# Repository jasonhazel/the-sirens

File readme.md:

# The Sirens

38/44/48/56 key split

## WORK IN PROGRESS

<p xmlns:cc="http://creativecommons.org/ns#" xmlns:dct="http://purl.org/dc/terms/"><a property="dct:title" rel="cc:attributionURL" href="https://github.com/jasonhazel/the-sirens">The Sirens</a> by <a rel="cc:attributionURL dct:creator" property="cc:attributionName" href="https://github.com/jasonhazel">Jason Hazel</a> is licensed under <a href="http://creativecommons.org/licenses/by/4.0/?ref=chooser-v1" target="_blank" rel="license noopener noreferrer" style="display:inline-block;">CC BY 4.0</a></p>

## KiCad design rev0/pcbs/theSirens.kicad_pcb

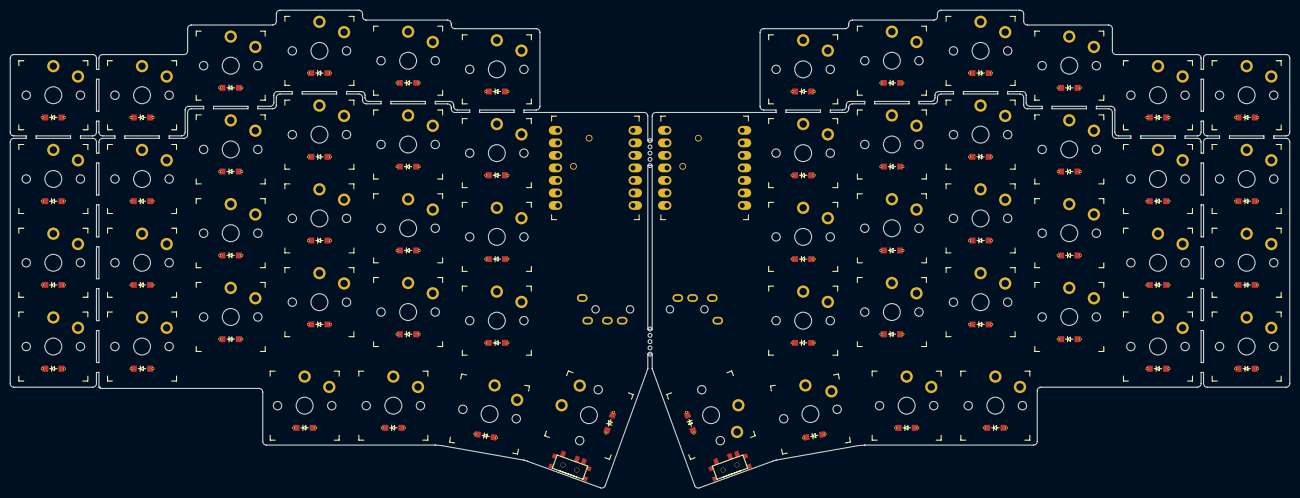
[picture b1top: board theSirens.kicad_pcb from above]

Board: 2 copper layers, 259.7 x 97.0 mm, 118 parts (0 on the bottom side), 78 nets, no tracks yet.

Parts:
74HC595, 74HC595#2: 74HC595_SOIC-16_3.9x9.9mm_P1.27mm
D1, D2, D3, D4, D5, D6, D7, D8, D9, D10, D11, D12, D13, D14, D15, D16, D17, D18, D19, D20, D21, D22, D23, D24, D25, D26, D27, D28, D29, D30, D31, D32, D33, D34, D35, D36, D37, D38, D39, D40, D41, D42, D43, D44, D45, D46, D47, D48, D49, D50, D51, D52, D53, D54, D55, D56: ComboDiode
S1, S2, S3, S4, S5, S6, S7, S8, S9, S10, S11, S12, S13, S14, S15, S16, S17, S18, S19, S20, S21, S22, S23, S24, S25, S26, S27, S28, S29, S30, S31, S32, S33, S34, S35, S36, S37, S38, S39, S40, S41, S42, S43, S44, S45, S46, S47, S48, S49, S50, S51, S52, S53, S54, S55, S56: PG1350
T1, T2: SPDT_C128955
XIAO1, XIAO2: xiao-ble-tht

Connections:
3V3: 74HC595.10, 74HC595.16, 74HC595#2.10, 74HC595#2.16, XIAO1.12, XIAO2.12
BAT: XIAO1.19, XIAO2.19
BAT-: T1.1, T2.1
GND: 74HC595.8, 74HC595.13, 74HC595#2.8, 74HC595#2.13, T1.2, T2.2, XIAO1.13, XIAO2.13
MISO: XIAO1.10, XIAO2.10
MOSI: 74HC595.14, 74HC595#2.14, XIAO1.11, XIAO2.11
RAW: XIAO1.14, XIAO2.14
RST: XIAO1.17, XIAO2.17
SCK: 74HC595.11, 74HC595#2.11, XIAO1.9, XIAO2.9
SR_CS: 74HC595.12, 74HC595#2.12
c0: 74HC595.1, 74HC595#2.1, S21.2, S22.2, S23.2, S24.2, S49.2, S50.2, S51.2, S52.2
c1: 74HC595.2, 74HC595#2.2, S17.2, S18.2, S19.2, S20.2, S45.2, S46.2, S47.2, S48.2
c2: 74HC595.3, 74HC595#2.3, S13.2, S14.2, S15.2, S16.2, S41.2, S42.2, S43.2, S44.2
c3: 74HC595.4, 74HC595#2.4, S9.2, S10.2, S11.2, S12.2, S37.2, S38.2, S39.2, S40.2
c4: 74HC595.5, 74HC595#2.5, S5.2, S6.2, S7.2, S8.2, S33.2, S34.2, S35.2, S36.2
c5: 74HC595.6, 74HC595#2.6, S1.2, S2.2, S3.2, S4.2, S29.2, S30.2, S31.2, S32.2
c6: 74HC595.7, 74HC595#2.7, S25.2, S26.2, S27.2, S28.2, S53.2, S54.2, S55.2, S56.2
index_bottom: D17.2, S17.1
index_home: D18.2, S18.1
index_numrow: D20.2, S20.1
index_top: D19.2, S19.1
inner_bottom: D21.2, S21.1
inner_home: D22.2, S22.1
inner_numrow: D24.2, S24.1
inner_thumbs: D28.2, S28.1
inner_top: D23.2, S23.1
middle_bottom: D13.2, S13.1
middle_home: D14.2, S14.1
middle_numrow: D16.2, S16.1
middle_thumbs: D27.2, S27.1
middle_top: D15.2, S15.1
mirror_index_bottom: D45.2, S45.1
mirror_index_home: D46.2, S46.1
mirror_index_numrow: D48.2, S48.1
mirror_index_top: D47.2, S47.1
mirror_inner_bottom: D49.2, S49.1
mirror_inner_home: D50.2, S50.1
mirror_inner_numrow: D52.2, S52.1
mirror_inner_thumbs: D56.2, S56.1
mirror_inner_top: D51.2, S51.1
mirror_middle_bottom: D41.2, S41.1
mirror_middle_home: D42.2, S42.1
mirror_middle_numrow: D44.2, S44.1
mirror_middle_thumbs: D55.2, S55.1
mirror_middle_top: D43.2, S43.1
mirror_outer_bottom: D29.2, S29.1
mirror_outer_home: D30.2, S30.1
mirror_outer_numrow: D32.2, S32.1
mirror_outer_thumbs: D54.2, S54.1
mirror_outer_top: D31.2, S31.1
mirror_pinky_bottom: D33.2, S33.1
mirror_pinky_home: D34.2, S34.1
mirror_pinky_numrow: D36.2, S36.1
mirror_pinky_top: D35.2, S35.1
mirror_reachy_thumbs: D53.2, S53.1
mirror_ring_bottom: D37.2, S37.1
mirror_ring_home: D38.2, S38.1
mirror_ring_numrow: D40.2, S40.1
mirror_ring_top: D39.2, S39.1
outer_bottom: D1.2, S1.1
outer_home: D2.2, S2.1
outer_numrow: D4.2, S4.1
outer_thumbs: D26.2, S26.1
outer_top: D3.2, S3.1
pinky_bottom: D5.2, S5.1
pinky_home: D6.2, S6.1
pinky_numrow: D8.2, S8.1
pinky_top: D7.2, S7.1
r0: D1.1, D5.1, D9.1, D13.1, D17.1, D21.1, D25.1, D29.1, D33.1, D37.1, D41.1, D45.1, D49.1, D53.1, XIAO1.4, XIAO2.4
r1: D2.1, D6.1, D10.1, D14.1, D18.1, D22.1, D26.1, D30.1, D34.1, D38.1, D42.1, D46.1, D50.1, D54.1, XIAO1.3, XIAO2.3
r2: D3.1, D7.1, D11.1, D15.1, D19.1, D23.1, D27.1, D31.1, D35.1, D39.1, D43.1, D47.1, D51.1, D55.1, XIAO1.2, XIAO2.2
r3: D4.1, D8.1, D12.1, D16.1, D20.1, D24.1, D28.1, D32.1, D36.1, D40.1, D44.1, D48.1, D52.1, D56.1, XIAO1.1, XIAO2.1
reachy_thumbs: D25.2, S25.1
ring_bottom: D9.2, S9.1
ring_home: D10.2, S10.1
ring_numrow: D12.2, S12.1
ring_top: D11.2, S11.1
x: 74HC595.15, 74HC595#2.15, XIAO1.5, XIAO1.6, XIAO1.7, XIAO1.8, XIAO2.5, XIAO2.6, XIAO2.7, XIAO2.8

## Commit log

2022-11-07 init
2022-11-18 first pcb
2022-11-18 remove backup
2022-11-18 remove autosave
2022-11-18 add ergogen yml
2022-11-18 add render
